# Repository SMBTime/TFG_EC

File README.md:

# TFG_EC

Diseño de un sistema electrónico monitorizado mediante FPGA.
  
--VHDL: Codigo y bancos de pruebas VHDL.

--Quartus: Proyecto de quartus para la carga en la FPGA.

--KICAD: Proyecto de kicad que contiene el esquematico desarrollado.

--ARDUINO: Codigo desarrollado para el microcontrolador.

--TFG_EC: Proyecto completo con todo el contenido desarrollado.

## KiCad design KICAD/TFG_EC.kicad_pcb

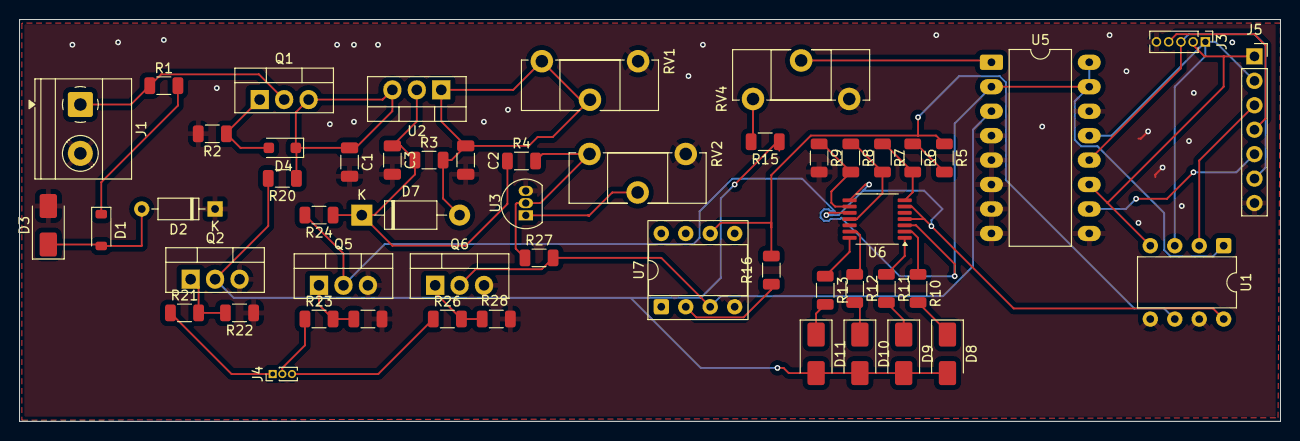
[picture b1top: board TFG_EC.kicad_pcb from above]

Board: 2 copper layers, 131.0 x 41.8 mm, 53 parts (0 on the bottom side), 42 nets.

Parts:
C1: 0.1uF; C_1206_3216Metric
C2: 10uF; C_1206_3216Metric
C3: 1uF; C_1206_3216Metric
D1: 1N4148W; D_SOD-123
D2: 1N4148W; D_DO-35_SOD27_P7.62mm_Horizontal
D3, D8, D9, D10, D11: LED; D_SMA
D4: 1N4741ATR; D_SOD-123F
D7: 1N4002; D_DO-41_SOD81_P10.16mm_Horizontal
J1: Conn_01x02_Pin; TerminalBlock_Phoenix_MKDS-1,5-2-5.08_1x02_P5.08mm_Horizont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
J3: Conn_01x05; PinHeader_1x05_P1.27mm_Vertical
J4: Conn_01x03; PinHeader_1x03_P1.00mm_Vertical
J5: Conn_01x07; PinSocket_1x07_P2.54mm_Vertical
Q1: IRF9540N; TO-220-3_Vertical
Q2, Q5, Q6: IRF540N; TO-220-3_Vertical
R1, R16: 2.2k; R_1206_3216Metric
R2: 22k; R_1206_3216Metric
R3: 240; R_1206_3216Metric
R4: 3.6k; R_1206_3216Metric
R5, R6, R7, R8, R9, R15, R22, R25, R28: 10k; R_1206_3216Metric
R10, R11, R12, R13: 6.8k; R_1206_3216Metric
R20, R24, R27: 470; R_1206_3216Metric
R21, R23, R26: 100; R_1206_3216Metric
RV1: 1k; Potentiometer_ACP_CA14-H4_Horizontal
RV2, RV4: 10k; Potentiometer_ACP_CA14-H4_Horizontal
U1: MCP4921-EP; DIP-8_W7.62mm
U2: LM317_TO-220; TO-220-3_Vertical
U3: LT1009xZ; TO-92L_Inline
U5: MCP3008; DIP-16_W10.16mm_LongPads
U6: LM339; TSSOP-14_4.4x5mm_P0.65mm
U7: OP07; DIP-8_W7.62mm_Socket

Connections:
+2.5V: R4.2, R27.1, RV2.3, U3.2 (K)
+2.5_F: R5.1, R16.2, U1.6 (VrefA), U7.6
+2.5_c: Q6.2 (D), R27.2, U5.3 (CH2), U7.3 (+)
+5V: C3.1, D7.1 (K), R3.1, R4.1, R24.1, U2.2 (VO)
+5V_c: Q5.2 (D), R24.2, U1.1 (VDD), U5.2 (CH1), U5.15 (Vref), U5.16 (Vdd), U6.3 (V+)
+12V: C1.1, D4.1 (K), Q1.3 (S), R20.1, U2.3 (VI)
+12V_c: D8.2 (A), D9.2 (A), D10.2 (A), D11.2 (A), Q2.2 (D), R15.1, R20.2, U7.7 (V+)
/3V: RV4.2, U5.1 (CH0)
/Vref-: C2.1, D7.2 (A), R3.2, RV1.2, RV1.3, U2.1 (ADJ)
CS1: J5.3, U1.2 (~CS)
CS2: J3.4, J5.4
CS3: J5.5, U5.10 (~CS/SHDN)
GND: C1.2, C2.2, C3.2, D2.1 (K), D3.2 (A), J1.2, J3.5, J5.7, Q2.3 (S), Q5.3 (S), Q6.3 (S), R2.2, R9.2, R22.1, R25.1, R28.1, RV1.1, RV2.1, RV4.3, U1.5 (~LDAC), U1.7 (AVSS), U3.3 (A), U5.4 (CH3), U5.5 (CH4), U5.6 (CH5), U5.7 (CH6), U5.8 (CH7), U5.9 (DGND), U5.14 (AGND), U6.12 (V-), U7.4 (V-)
MOSFET_2.5V: J4.3, R26.1
MOSFET_5V: J4.2, R23.1
MOSFET_12V: J4.1, R21.1
unnamed: D1.2 (A), D2.2 (A), D3.1 (K)
unnamed: D1.1 (K), R1.2
unnamed: D4.2 (A), Q1.1 (G), R2.1
unnamed: D8.1 (K), R10.2
unnamed: D9.1 (K), R11.2
unnamed: D10.1 (K), R12.2
unnamed: D11.1 (K), R13.2
unnamed: J1.1, Q1.2 (D), R1.1
unnamed: Q2.1 (G), R21.2, R22.2
unnamed: Q5.1 (G), R23.2, R25.2
unnamed: Q6.1 (G), R26.2, R28.2
unnamed: R10.1, U6.2
unnamed: R11.1, U6.1
unnamed: R12.1, U6.13
unnamed: R13.1, U6.14
unnamed: R15.2, RV4.1
unnamed: RV2.2, U3.1 (FB)
unnamed: R5.2, R6.1, U6.5 (+)
unnamed: R6.2, R7.1, U6.7 (+)
unnamed: R7.2, R8.1, U6.11 (+)
unnamed: R8.2, R9.1, U6.9 (+)
unnamed: R16.1, U7.2 (-)
SCK: J3.1, J5.2, U1.3 (SCK), U5.13 (CLK)
SDI: J3.2, J5.1, U1.4 (SDI), U5.11 (Din)
SDO: J3.3, J5.6, U5.12 (Dout)
Vsel: U1.8 (VoutA), U6.4 (-), U6.6 (-), U6.8 (-), U6.10 (-)

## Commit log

2025-06-06 SUBIDA 1
2025-06-06 SUBIDA 2
2025-06-10 ARDUINO
2025-06-10 KICAD
2025-06-10 VHDL
2025-06-10 QUARTUS
2025-06-10 TFG COMPLETO
